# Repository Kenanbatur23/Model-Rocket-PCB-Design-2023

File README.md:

# Model-Rocket-PCB-Design-2023
avionics system for model rocket, this project was designed using eagle
<br/>
[My Linkedin Profile](https://www.linkedin.com/in/kenan-batur-b55540196/)<br/>
<br/>
<br/>
<br/>
<br/>
<br/>
<br/>
<br/>
<br/>
<br/>

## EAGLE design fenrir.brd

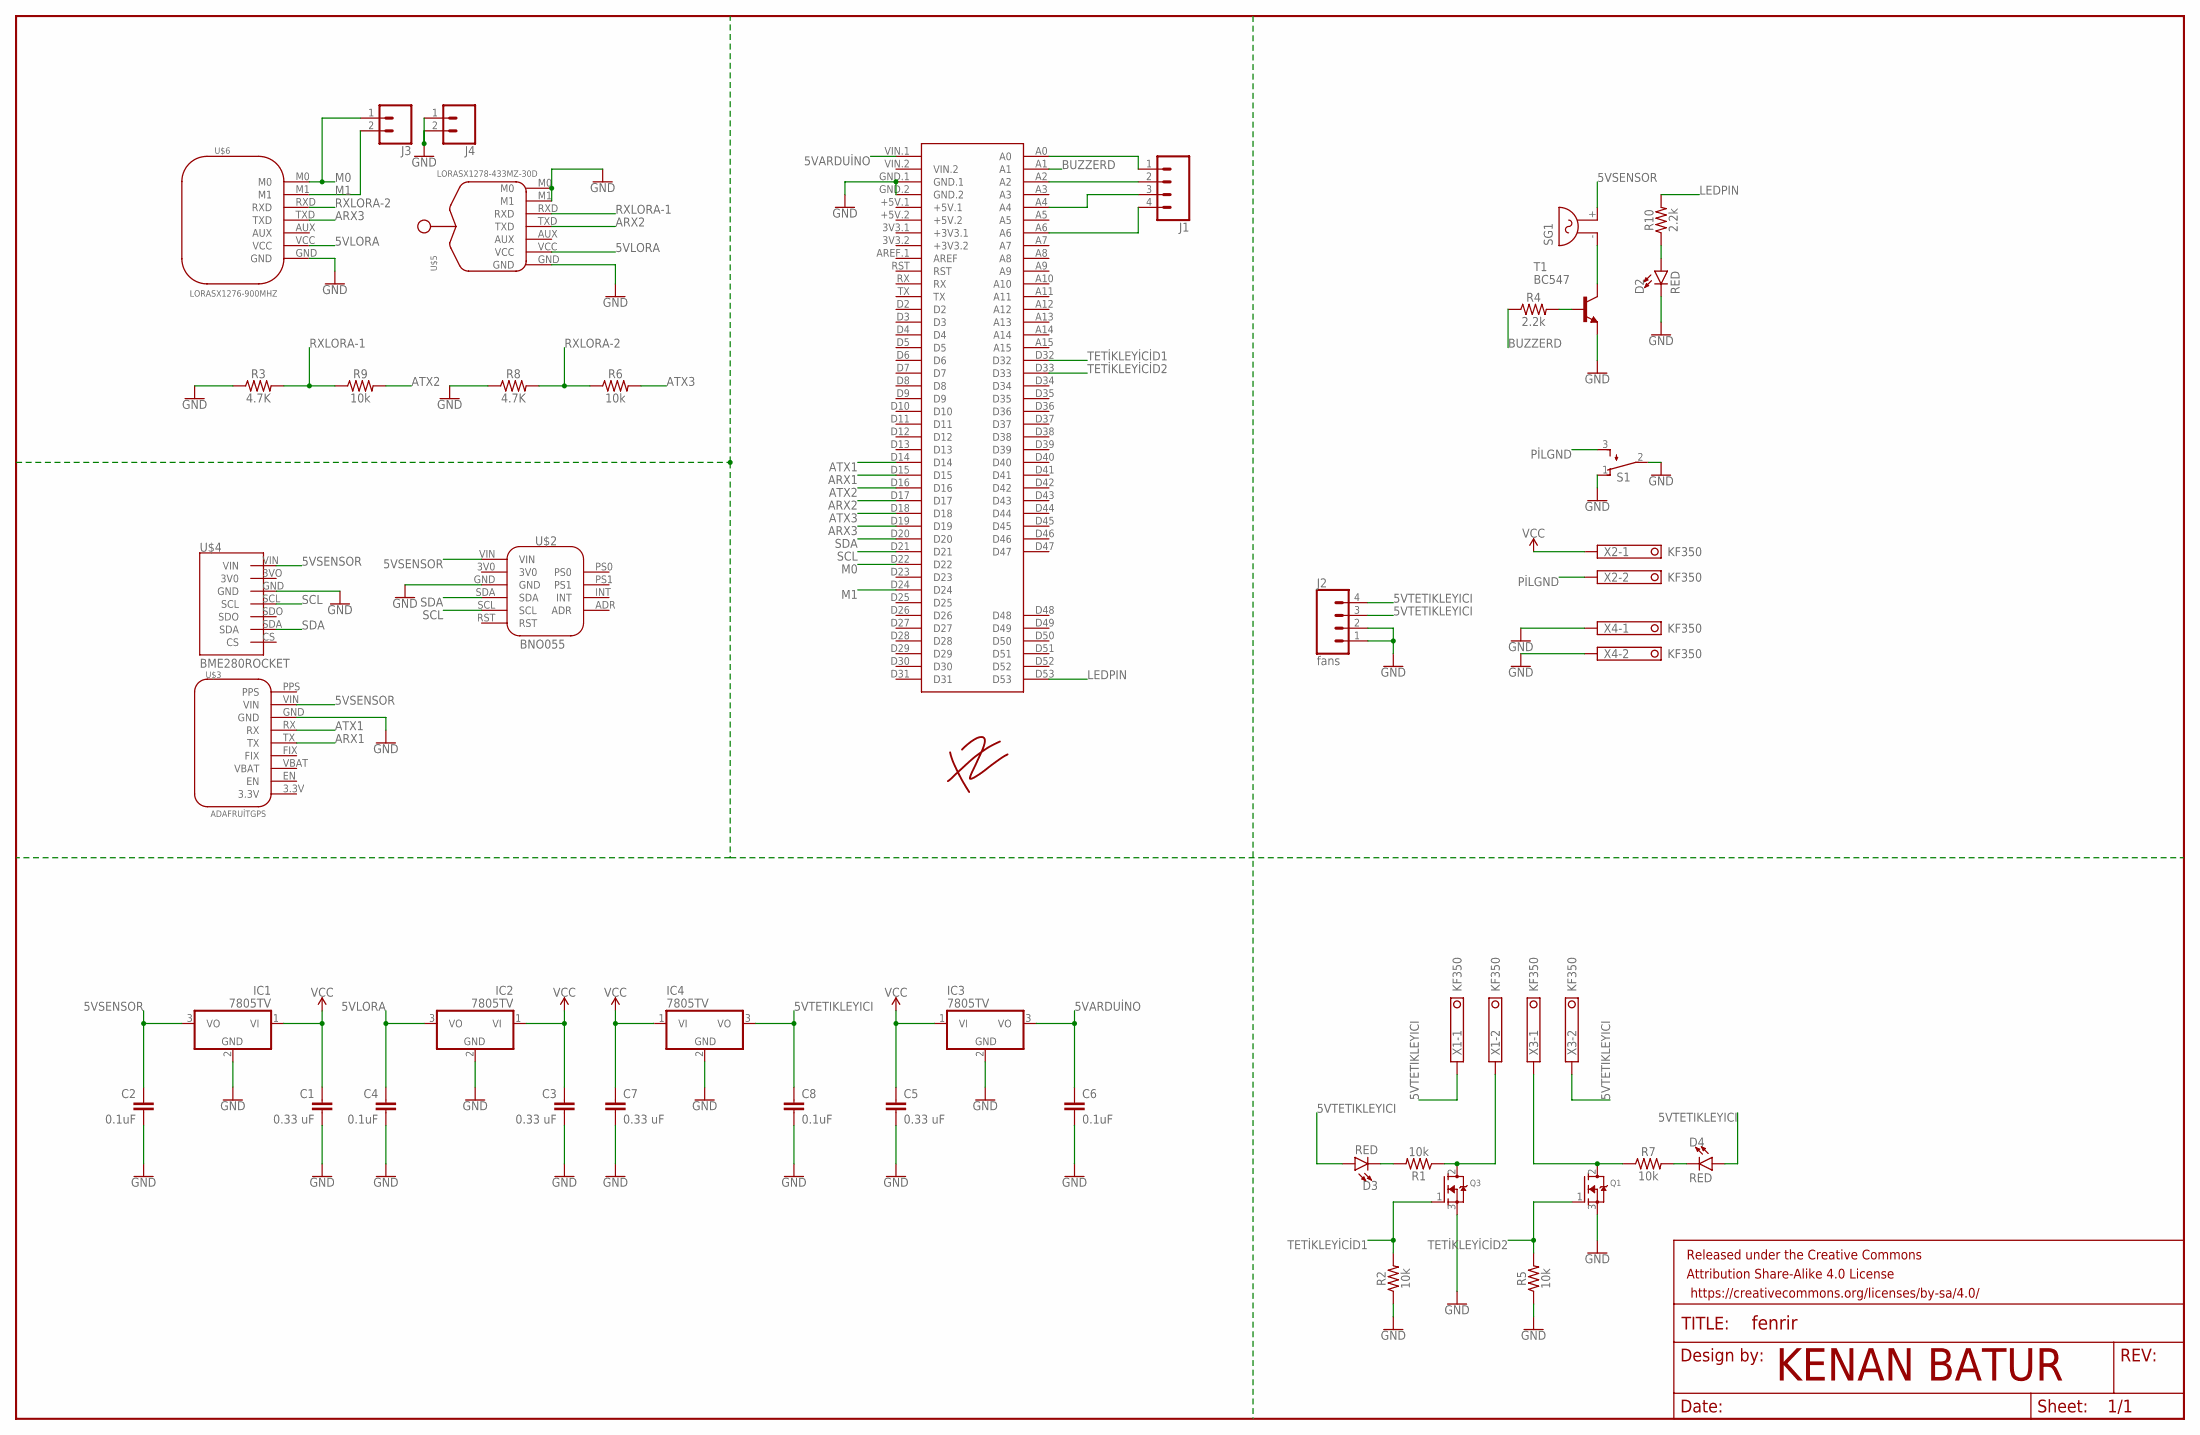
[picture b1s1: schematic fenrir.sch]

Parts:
C1, C3, C5, C7: 0.33 uF; C2.5-3
C2, C4, C6, C8: 0.1uF; C2.5-3
D2, D3, D4: RED; LED-1206
FRAME2: FRAME-LEDGER; CREATIVE_COMMONS
IC1, IC2, IC3, IC4: 7805TV; TO220V
J1: CONN_04; 1X04
J2: fans; 1X04
J3, J4: CONN_02; 1X02
Q1, Q3: MOSFET-NGDS_TO220V; TO220V
R1, R2, R5, R6, R7, R9: 10k; AXIAL-0.3
R3, R8: 4.7K; AXIAL-0.3
R4, R10: 2.2k; AXIAL-0.3
S1: TL32PO; TL3XPO
SG1: F/QMX
T1: BC547; TO92
U$1: MEGA2560_MIKRO
U$2: BNO055
U$3: ADAFRUİTGPS
U$4: BME280ROCKET
U$5: LORASX1278-433MZ-30D; LORASX1278-433MHZ-30D
U$6: LORASX1276-900MHZ; LORASX1278-433MHZ
U$7: MAVİLOGO; LOGOMAVİ
X1, X2, X3, X4: KF350; TERMINAL-BLOCK-2-PIN-3.5MM-ROUND-PAD

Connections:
5VARDUİNO: C6.1, IC3.3 (VO), U$1.VIN.1
5VLORA: C4.1, IC2.3 (VO), U$5.VCC, U$6.VCC
5VSENSOR: C2.1, IC1.3 (VO), SG1.+ (2), U$2.VIN, U$3.VIN, U$4.VIN
5VTETIKLEYICI: C8.1, D3.A, D4.A, IC4.3 (VO), J2.3, J2.4, X1.1, X3.2
ARX1: U$1.D15, U$3.TX
ARX2: U$1.D17, U$5.TXD
ARX3: U$1.D19, U$6.TXD
ATX1: U$1.D14, U$3.RX
ATX2: R9.P$2 (2), U$1.D16
ATX3: R6.P$2 (2), U$1.D18
BUZZERD: R4.P$1 (1), U$1.A1
GND: C1.2, C2.2, C3.2, C4.2, C5.2, C6.2, C7.2, C8.2, D2.C, IC1.2 (GND), IC2.2 (GND), IC3.2 (GND), IC4.2 (GND), J2.1, J2.2, J4.1, J4.2, Q1.3 (S), Q3.3 (S), R2.P$1 (1), R3.P$1 (1), R5.P$1 (1), R8.P$1 (1), S1.1 (O), S1.2, T1.1 (E), U$1.GND.1, U$1.GND.2, U$2.GND, U$3.GND, U$4.GND, U$5.GND, U$5.M0, U$5.M1, U$6.GND, X4.1, X4.2
LEDPIN: R10.P$2 (2), U$1.D53
M0: J3.1, U$1.D22, U$6.M0
M1: J3.2, U$1.D24, U$6.M1
unnamed: Q3.2 (D), R1.P$1 (1), X1.2
unnamed: SG1.- (1), T1.3 (C)
unnamed: J1.1, U$1.A0
unnamed: D3.C, R1.P$2 (2)
unnamed: D4.C, R7.P$2 (2)
unnamed: Q1.2 (D), R7.P$1 (1), X3.1
unnamed: R4.P$2 (2), T1.2 (B)
unnamed: J1.2, U$1.A2
unnamed: J1.3, U$1.A4
unnamed: J1.4, U$1.A6
unnamed: D2.A, R10.P$1 (1)
PİLGND: S1.3 (S), X2.2
RXLORA-1: R3.P$2 (2), R9.P$1 (1), U$5.RXD
RXLORA-2: R6.P$1 (1), R8.P$2 (2), U$6.RXD
SCL: U$1.D21, U$2.SCL, U$4.SCL
SDA: U$1.D20, U$2.SDA, U$4.SDA
TETİKLEYİCİD1: Q3.1 (G), R2.P$2 (2), U$1.D32
TETİKLEYİCİD2: Q1.1 (G), R5.P$2 (2), U$1.D33
VCC: C1.1, C3.1, C5.1, C7.1, IC1.1 (VI), IC2.1 (VI), IC3.1 (VI), IC4.1 (VI), X2.1

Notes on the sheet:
KENAN BATUR

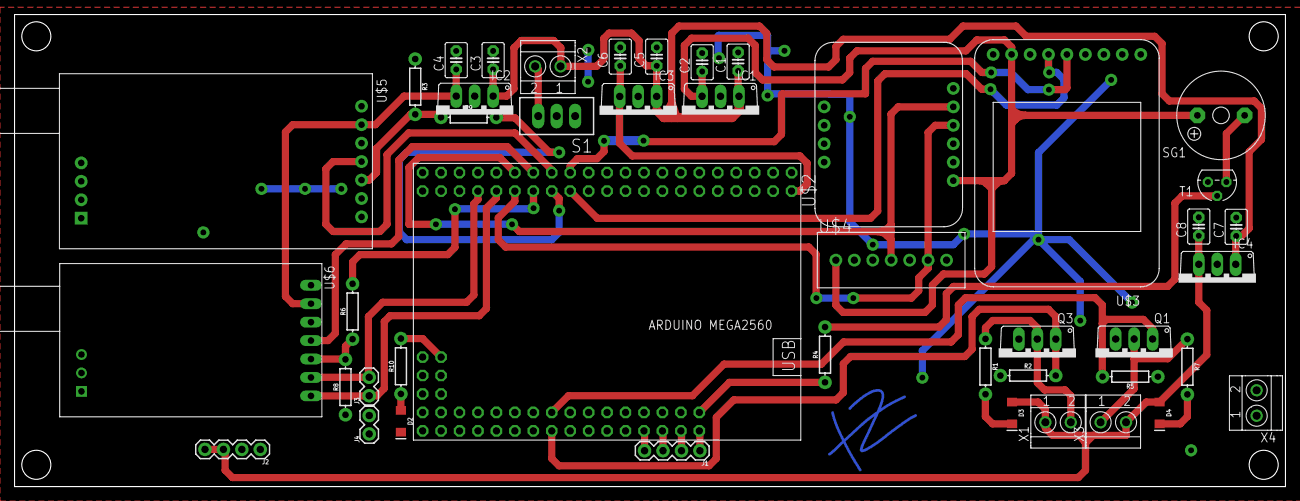
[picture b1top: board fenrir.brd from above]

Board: 2 copper layers, 175.0 x 65.0 mm, 46 parts (0 on the bottom side), 34 nets.

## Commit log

2023-04-29 image

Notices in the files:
parts and their libraries:
SparkFun-LED: Licensing: Creative Commons ShareAlike 4.0 International - https://creativecommons.org/licenses/by-sa/4.0
SparkFun-Aesthetics: Released under the Creative Commons Attribution Share-Alike 4.0 License
SparkFun-Aesthetics: https://creativecommons.org/licenses/by-sa/4.0
